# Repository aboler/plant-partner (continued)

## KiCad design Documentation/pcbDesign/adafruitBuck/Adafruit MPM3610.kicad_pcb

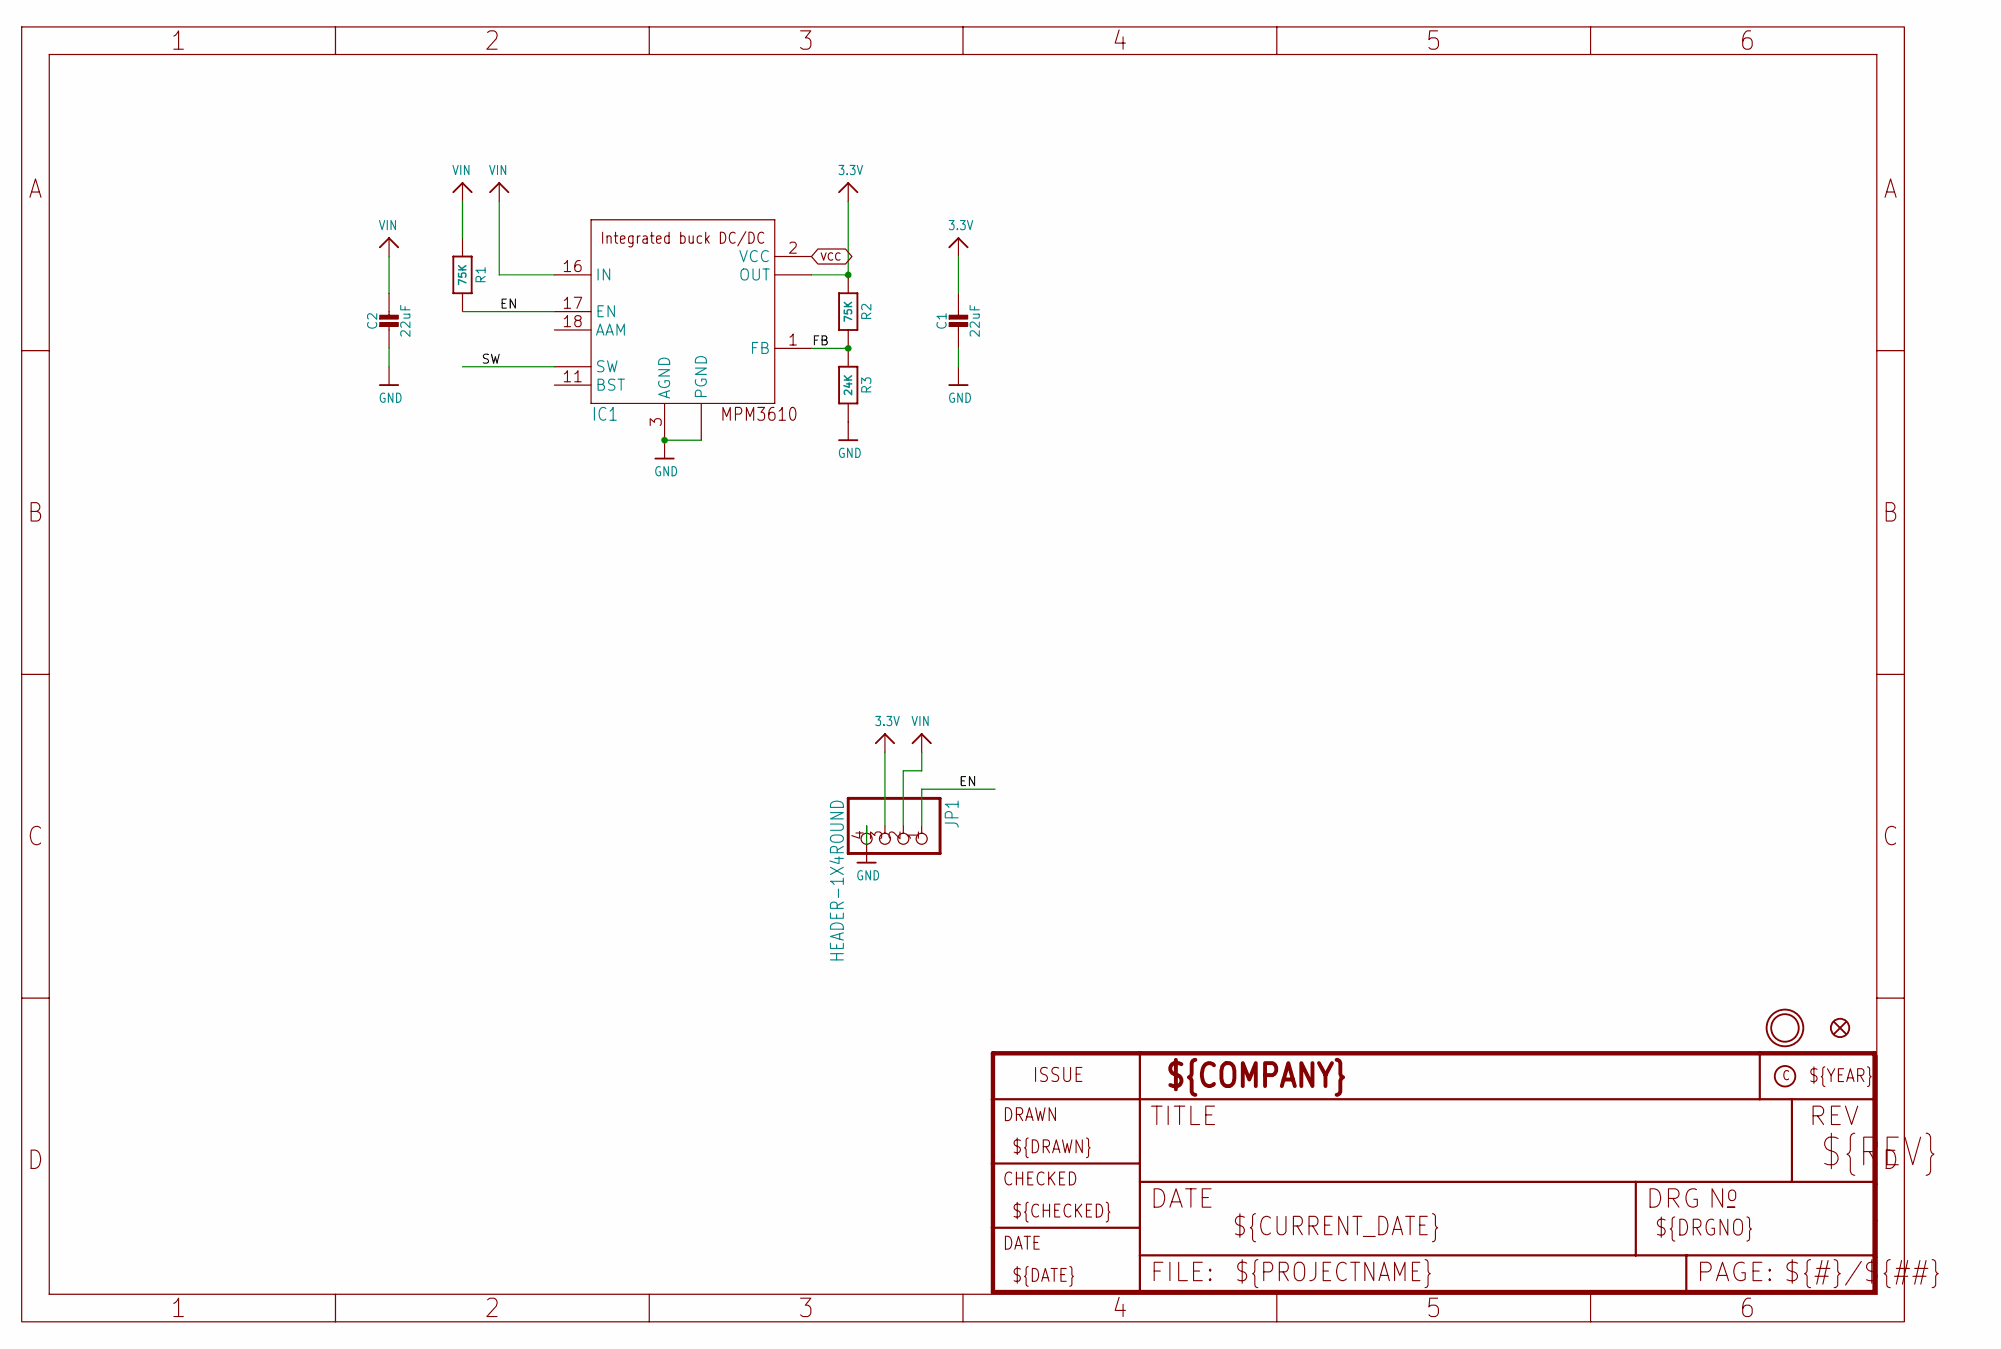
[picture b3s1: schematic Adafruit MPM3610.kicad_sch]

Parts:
C1, C2: 22uF; 0805-NO
FID1: FIDUCIAL_1MM
IC1: MPM3610
JP1: HEADER-1X4ROUND; 1X04_ROUND
R1, R2: 75K; 0603-NO
R3: 24K; 0603-NO
U$9: MOUNTINGHOLE2.5; MOUNTINGHOLE_2.5_PLATED

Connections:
3.3V: C1.1, IC1.7 (OUT), IC1.8 (OUT), IC1.9 (OUT), JP1.3, R2.1
EN: IC1.17 (EN), JP1.1, R1.2
FB: IC1.1 (FB), R2.2, R3.1
GND: C1.2, C2.2, IC1.3 (AGND), IC1.12 (PGND), IC1.13 (PGND), IC1.14 (PGND), JP1.4, R3.2
SW: IC1.4 (SW), IC1.5 (SW), IC1.6 (SW)
VCC: IC1.2 (VCC)
VIN: C2.1, IC1.16 (IN), JP1.2, R1.1

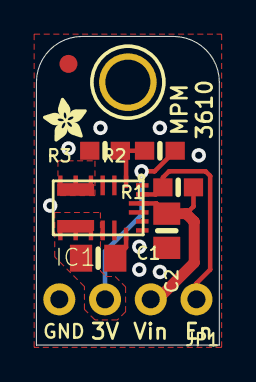
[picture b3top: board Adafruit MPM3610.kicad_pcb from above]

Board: 2 copper layers, 10.2 x 17.1 mm, 11 parts (1 on the bottom side), 6 nets.

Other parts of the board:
U$10: PCBFEAT-REV-040
U$11: ADAFRUIT_2.5MM

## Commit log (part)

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2025-11-11 Save point
2025-11-11 fixed
2025-11-11 Updated TimeSheet
2025-11-11 Nicholas - Updated Timesheet
2025-11-13 Update start time
2025-11-13 Wifi build on my laptop now
2025-11-13 Updated main to only update voltage for photoresistor ADC upon switch0 change
2025-11-13 Made updated main to active and deactive external motor
2025-11-13 Changed file names because it technically has inputs now
2025-11-13 Updated start/end time, able to display data from backend onto homescreen, currently unformatted
2025-11-13 Nicholas - Timesheet checkup
2025-11-13 GUYS THE MOTOR WORKS
2025-11-13 Accidentally broke build in merge, but it's fixed now I swear
2025-11-14 https get configured dirty
2025-11-14 Changed folder name containing timesheets according to requirements, added start time
2025-11-14 Update end time
2025-11-14 Pushed completed circuit onto Github
2025-11-14 Updated time/description in timesheet
2025-11-14 Changed post.dart to plant, changed the format to reflect one plant
2025-11-14 Refactor remote_service, return Plant through function getPlant
2025-11-14 Upload circuit diagrams for prototype
2025-11-14 Prepare for merging to main
2025-11-14 Update end time - Sabrina timesheet
2025-11-15 Able to receive data from NPK Sensor but need to test which registers actually output N-P-K values and not 00 or random values
2025-11-15 I will start testing individual register values when I can
2025-11-15 First idea of script is down. Time to test and iterate
2025-11-15 Update README.md to include new documentation dirs
2025-11-15 I'm taking a break brb
2025-11-15 refactored and restructured requests
2025-11-15 I'm back
2025-11-16 Finished up scripts and python script to make running esp-32 easier
2025-11-16 Modify timesheet
2025-11-16 Update README.md to reflect current progress and start how to run
2025-11-16 Updated ReadMe to show cloud changes
2025-11-16 update submodules maybe doesnt break now
2025-11-16 clutch debug
2025-11-16 Putting change for moisture
2025-11-16 wifi reconnect test button
2025-11-16 Timesheet update
2025-11-17 Tested on Windows and it properly works
2025-11-17 Added NPK Sensor Diagram to Diagrams/
2025-11-17 Testing running frontend and backend on same local machine
2025-11-17 Nicholas - Updated README, Software Release to include the steps to running the backend server
2025-11-17 Updated README with frontend application information
2025-11-18 Added RS485 Transceiver and progressed with ESP32 and 12V Relay
2025-11-18 test
2025-12-01 stash changes
2025-12-01 Prototype demo changes. Small things for testing
2025-12-01 stash
2026-01-06 Implemented 5V Relay to our specs. Time to verify it and add AC to 12V Adapter to overall schematic then draw PCB
2026-01-08 ADC reworked and confirmed to function correctly
2026-01-08 Variable organization
2026-01-08 Removed interrupts from GPIO + started blinky peripheral
2026-01-09 Heartbeat in and works
2026-01-09 update timesheet end
2026-01-09 Remove comment
2026-01-12 Minor grammar fix
2026-01-16 Yayyyy debuging -_-
2026-01-17 Tested and confirmed works + cleanups
2026-01-17 Removed typo
2026-01-21 Add pin usage diagram
2026-01-21 Added end time
2026-01-23 Nicholas: Set up working MQTT client on the BackEnd with tested pushlishing of Control Messages
2026-01-23 Included check-in meeting time
2026-01-23 Done
2026-01-24 Added hours from meeting today and winter break
2026-01-24 Update time report
2026-01-26 Motor wires have been elongated
2026-01-26 Jk lemme put this in a different branch
2026-01-26 Verified circuit. Time to finalize Schematic with symbols that have compatible footprints. Need to add remaining 3D models, testing pins for PCB, and verify relay octocoupler footprint + symbol
2026-01-26 Connected to new circuit htat I built and test newly soldered motor and it works
2026-01-28 Put in the correct ESP32 (DEVKIT-V1) into Schematic. Updated the IO pin connections for ESP. Added Power supply system to SChematic. Need to update optocoupler symbol and footprint. Then routing shal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
2026-01-29 creating task layout w placeholder and adding task button
2026-01-29 add autoschedule flag to plant model
2026-01-29 implement autoscheduling toggle with backend state
2026-01-30 need to test on lunch break
2026-01-31 Fixed optocoupler for Relay circuits
2026-01-31 blur backend ip
2026-02-04 foundation
2026-02-05 add functions
2026-02-05 syntax
2026-02-05 switch
2026-02-05 need to pull from main
2026-02-05 Autoschedule task implemented in backend + frontend
2026-02-05 Updating main with autoschedule
2026-02-05 Added a small note to schematic
2026-02-05 Restructure done
2026-02-06 Updated Timesheet since I messed it up earlier today
2026-02-06 We showed off the Alpha Build to Tyler and I worked on the PCB Routing. I am trying to resolve the Electrical Rules Checker (ERC) now while routing.
2026-02-08 Routed the 5V Relays and fixed a schematic issue I made with them. Next is the Buck Converter, RS485 Transceiver, Power Supplies, and ESP32 Signals
2026-02-08 Leftover backups from KiCad
2026-02-10 simpler read
2026-02-10 CHANGE IP!!!
2026-02-10 checkpt
2026-02-10 Fixed Buck Converter and routed it. Connected more majority of ESP signals and some of the debugging pins. Brought the size of PCB down to about 1/2 of the original. My goal is to finish by today and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
2026-02-10 Mosquitto config file, allow publishing from external connection
2026-02-11 Update Documentation before beginning more work
2026-02-11 Stopping point for today; rerouted directories and organized
2026-02-11 Comment/space adjustment, yaknow the usual
2026-02-11 Update doc
2026-02-11 I think all code is in place to test if we get anything in lab tomorrow
2026-02-11 Put in end time
2026-02-12 Finished Routing (for now). I need to add silkscreens for debugging, then copper pour and probably other stuff. My goal is so have a JLCPCB order by tomorrow. I brought the PCB down to about the size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
2026-02-12 add end time
2026-02-12 Testing mqtt frontend temp
2026-02-12 Testing mqtt functionality from app
2026-02-12 Updated pins, test didn't work :(
2026-02-13 Finished Labeling PCB (too much) and fixed DRC errors on PCB. Time to add copper pours, drill holes, and probably more, then review it with a TA, and make the order :)
2026-02-13 I just need to see what's going wrong here if anything
2026-02-13 pt 2
2026-02-13 Meeting with Tyler. I tried to implement Lamp Circuit with MOSFET but having trouble simulating it in LTspice
2026-02-15 Added Lamp to PCB. Added Copper Pours and Drill Holes. Now fixing rude error about cap. not getting copper pour connection properly
2026-02-15 Ok things to try in lab: see if this set up works, see if clock used on other components ( heartbeat, pwm) is intefering
2026-02-16 Gerber and Drill files have been generated. I will order on JLCPCB tomorrow morning ASAP and then finish up cube for Beta
2026-02-16 Fixed comment
2026-02-17 Finalizing some more stuff (grrrr) for JLCPCB printing
2026-02-17 Change sample endpoint, cleanup main
2026-02-17 Better visual feedback for toggling buttons on bottom nav
2026-02-17 Wifi want spaces
2026-02-18 Check for today, changed led pin
2026-02-19 Nicholas - First test completed for Backend to addresss tasks and send control signals as need
2026-02-19 I got the plugin finally working! I had some messed up Python modules that I had to remove and then reinstall. I have also now learned that the footprints I chose for the PCB were too small and class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
2026-02-19 Individual buttons to trigger sensors
2026-02-19 quick fixes
2026-02-20 Started JLCPCB order process. Need to evaluate cheapest options, out-of-stock replacements, and parts JLCPCB does not have at all
2026-02-20 Task functionality and individual sensors triggered, not clean but need for main
2026-02-20 Nicholas - Made backend's communication to Micro more sophisticated with specific tasks to complete. Also edited frontend code to be able to run frontend and backend on the same machine for testing.
2026-02-20 Final beta docs
2026-02-20 I ordered the PCBgit add . … there is so many changes I want to make but I also just wanted to order it but without the revisions it was more expensive but now we at least will have a board. Welp, ei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
2026-02-23 Demo ready:
2026-02-24 Added Thread Size to pump doc
2026-02-24 Added basic implementation of 2.0 changes to see how much cheaper new PCB would be. As of now, it is half the price :O
2026-02-26 Cleaning up MOSFET circuits
2026-02-27 Made some timing changes to make ti easier to demo
2026-03-01 Routed v2 PCB some more. Finished routing power sources, Buck Converter, MOSFET circuits, and most of RS485 Transceiver. I forgot about KiCad but will not next time I get a big chunk of time
2026-03-01 File name organization in docs.
2026-03-01 New idf version had silly include error, fixed it
2026-03-02 Nicholas - temp decrease of cycle interval from 60 seconds to 30 seconds for testing
2026-03-02 Update hours
2026-03-03 Nicholas - temp update
2026-03-03 For fun
2026-03-03 Made it so main is really sweet and nice and keeps sending http data until its sure the database will receive
2026-03-03 Modified names/types
2026-03-03 Ordered PCB v2 after verifying MOSFET PWM circuits in Ltspicegit add . It was definitely cheaper but still just over 0 for all 5 to be assembled with SMT parts. Next I’ll work on “solving” the NPK so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
2026-03-04 Made documentation naming consistent
2026-03-04 I got it working! I adjusted the CRC checker and added a delay when switching between Receive and Transmit mode. The data looks valid and increases or decreases when in or out of dirt. Next I'll clea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
2026-03-04 Reporting Timesheet
2026-03-10 Update README.md syntax
2026-03-10 Update to fit current version
2026-03-10 Adjusted formatting
2026-03-11 Should actually send npk data to app now
2026-03-11 So now fertilizer pump should only occur if sum is under 60 (temp)
2026-03-11 Finish time
2026-03-12 tested handshake
2026-03-12 Nicholas - Functionality for full communications and error message passing with the microcontroller implemented on the backend
2026-03-12 Carter confirmed, don't need. Also yay it works
2026-03-15 Update time/materials, place onshape link
2026-03-15 Add diagrams
2026-03-17 adjusted logic
2026-03-23 add ringbuffer library
2026-03-23 better library
2026-03-24 Updating Timesheet ... yeah I got no idea why I didn't merge my latest timesheet into main lol
2026-03-26 Updated Timesheet for 3D modeling
2026-03-28 add start
2026-03-31 mergeco
2026-03-31 Fix esp-idf submodule to match main
2026-03-31 match idf version from old commit
2026-03-31 Extended time testing and appDev
2026-03-31 Remove test
2026-03-31 message for 5 seconds when trigger sensors
2026-03-31 Updated Pins for ESP32 on new PCB
2026-03-31 Merged main in and nothing broke with new pin assignments (it compiled)
2026-03-31 Revert IP and fix led pin, ALSO PCB WORKS
2026-03-31 Updating Timesheet
2026-03-31 Update end time and pinouts
2026-04-02 Listening to mqtt messages from frontend, more dropdown options
2026-04-02 Common ip var
2026-04-02 Nicholas - updated backend so autosampling works.
2026-04-02 Merriweather Sans text theme
2026-04-03 task, calendar start and end
2026-04-03 Updated Timesheet and Release Candidate meeting w/ Tyler
2026-04-06 placeholder, no actuation
2026-04-06 Nicholas - Updated backend to take care of tasks at their proper end time, and new task topic for tasks added.
2026-04-14 Edit spacing
2026-04-14 Update contirbutions
2026-04-14 adding days to task
2026-04-14 dependecies
2026-04-14 dependencies
2026-04-14 Should work lol
2026-04-17 Swap ip
2026-04-17 Added default value for Topic Task Menu check that just samples values if water, light, or nutrient sensor message not sent
2026-04-17 change
2026-04-20 Nicholas - Shortened interval at which tasks are checked from 30 seconds to 20 seconds.
2026-04-21 back to 30 mwehehe
2026-04-21 prep
